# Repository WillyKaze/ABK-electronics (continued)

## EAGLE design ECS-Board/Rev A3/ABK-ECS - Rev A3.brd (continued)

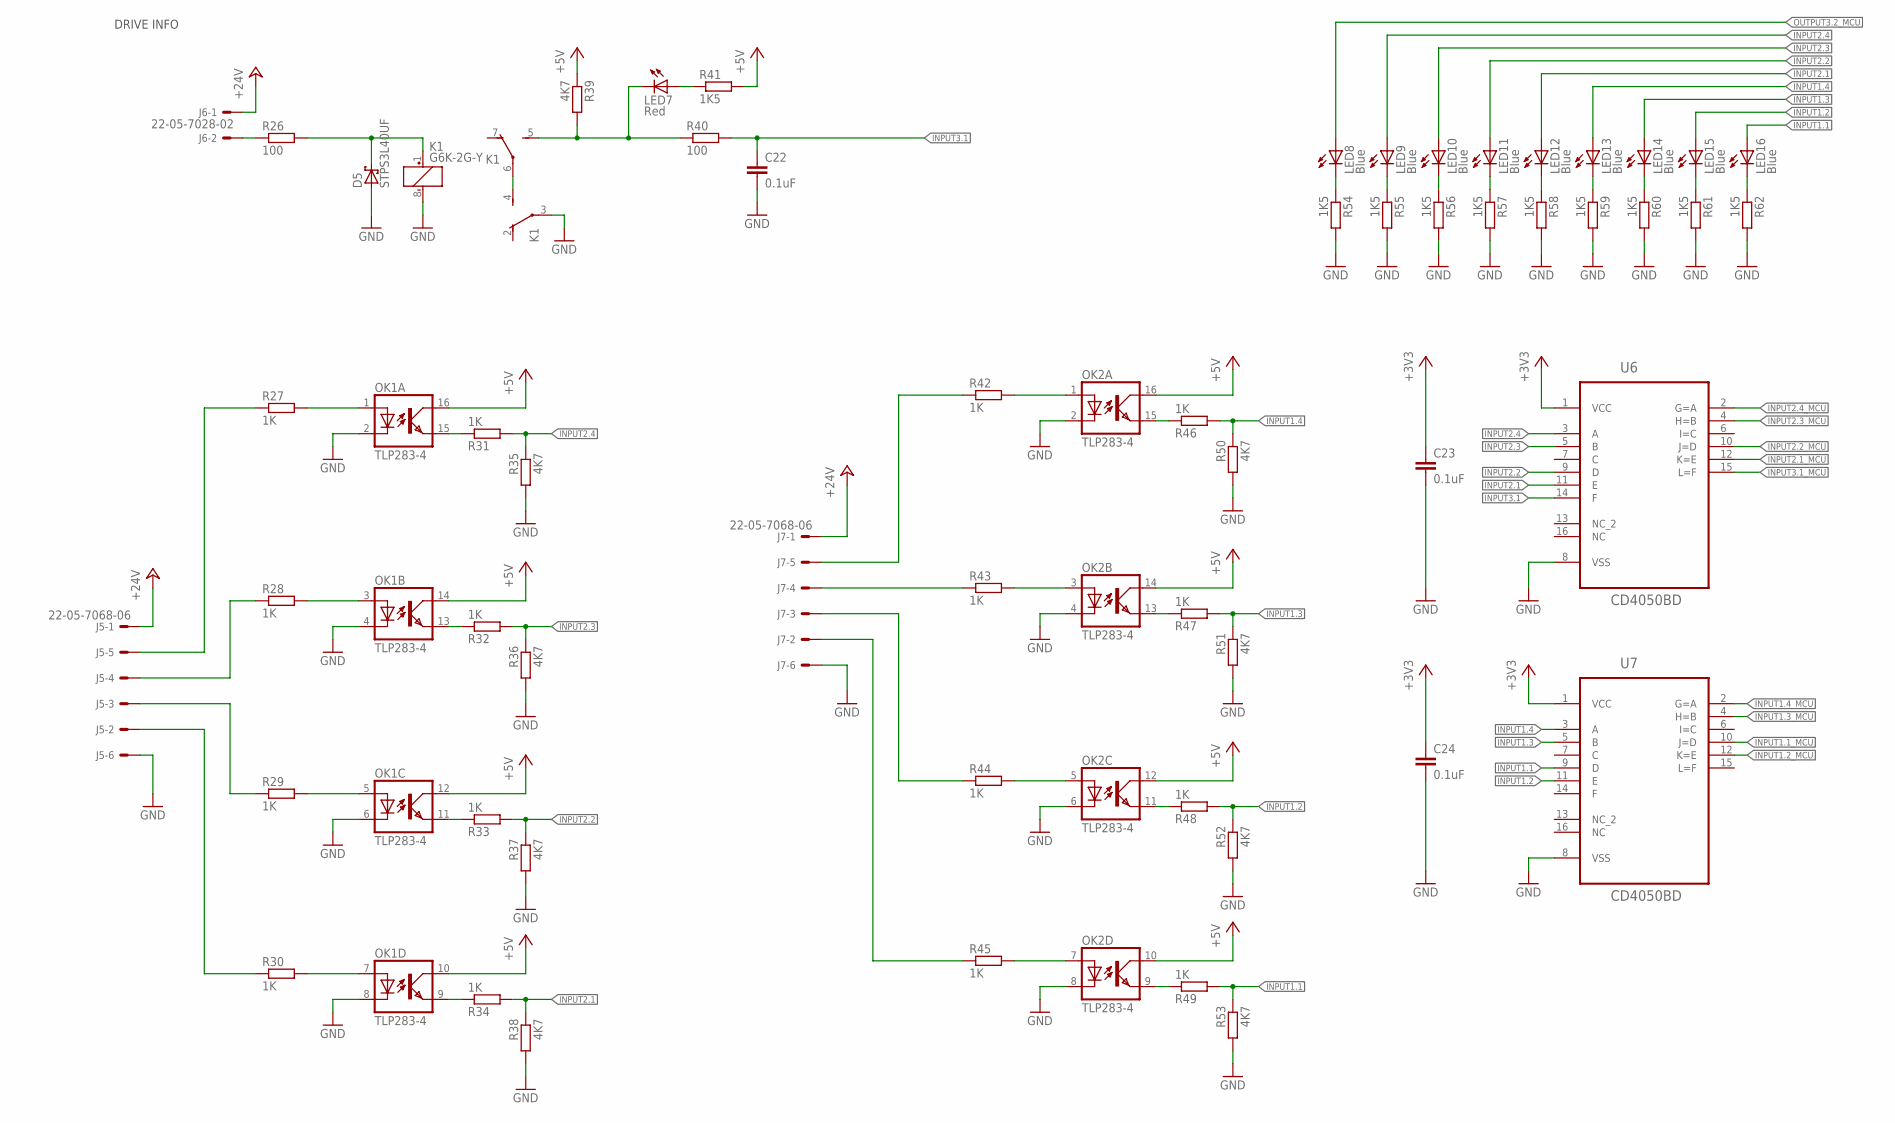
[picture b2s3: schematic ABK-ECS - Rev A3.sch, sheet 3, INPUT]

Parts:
C22, C23, C24: 0.1uF; C0603; MPN MC0603B104K160CT
D5: STPS3L40UF; SMB
J5, J7: 22-05-7068-06; 7395-06
J6: 22-05-7028-02; 7395-02; MPN 22-05-7028
K1: G6K-2G-Y; MPN G6K-2G-Y 24DC
LED7: Red; CHIPLED_0603; MPN OVS-0608
LED8, LED9, LED10, LED11, LED12, LED13, LED14, LED15, LED16: Blue; CHIPLED_0603; MPN OVS-0603
OK1, OK2: TLP283-4; MINI-FLAT-16; MPN TCMT4100
R26, R40: 100; R0603; MPN RC0603FR-13100RL
R27, R28, R29, R30, R31, R32, R33, R34, R42, R43, R44, R45, R46, R47, R48, R49: 1K; R0603; MPN RC0603FR-071KL
R35, R36, R37, R38, R39, R50, R51, R52, R53: 4K7; R0603; MPN RC0603FR-074K7L
R41, R54, R55, R56, R57, R58, R59, R60, R61, R62: 1K5; R0603; MPN RC0603FR-071K5L
U6, U7: CD4050BD; SOIC127P600X175-16N

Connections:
+3V3: C23.1, C24.1, U6.1 (VCC), U7.1 (VCC); also elsewhere on the board
+5V: OK1.10 (COL), OK1.12 (COL), OK1.14 (COL), OK1.16 (COL), OK2.10 (COL), OK2.12 (COL), OK2.14 (COL), OK2.16 (COL), R39.1, R41.2; also elsewhere on the board
+24V: J5.1, J6.1, J7.1; also elsewhere on the board
GND: C22.2, C23.2, C24.2, D5.A, J5.6, J7.6, K1.3, K1.8 (-), OK1.2 (C), OK1.4 (C), OK1.6 (C), OK1.8 (C), OK2.2 (C), OK2.4 (C), OK2.6 (C), OK2.8 (C), R35.2, R36.2, R37.2, R38.2, R50.2, R51.2, R52.2, R53.2, R54.2, R55.2, R56.2, R57.2, R58.2, R59.2, R60.2, R61.2, R62.2, U6.8 (VSS), U7.8 (VSS); also elsewhere on the board
INPUT1.1: LED16.A, R49.2, R53.1, U7.9 (D)
INPUT1.1_MCU: U7.10 (J=D); also elsewhere on the board
INPUT1.2: LED15.A, R48.2, R52.1, U7.11 (E)
INPUT1.2_MCU: U7.12 (K=E); also elsewhere on the board
INPUT1.3: LED14.A, R47.2, R51.1, U7.5 (B)
INPUT1.3_MCU: U7.4 (H=B); also elsewhere on the board
INPUT1.4: LED13.A, R46.2, R50.1, U7.3 (A)
INPUT1.4_MCU: U7.2 (G=A); also elsewhere on the board
INPUT2.1: LED12.A, R34.2, R38.1, U6.11 (E)
INPUT2.1_MCU: U6.12 (K=E); also elsewhere on the board
INPUT2.2: LED11.A, R33.2, R37.1, U6.9 (D)
INPUT2.2_MCU: U6.10 (J=D); also elsewhere on the board
INPUT2.3: LED10.A, R32.2, R36.1, U6.5 (B)
INPUT2.3_MCU: U6.4 (H=B); also elsewhere on the board
INPUT2.4: LED9.A, R31.2, R35.1, U6.3 (A)
INPUT2.4_MCU: U6.2 (G=A); also elsewhere on the board
INPUT3.1: C22.1, R40.2, U6.14 (F)
INPUT3.1_MCU: U6.15 (L=F); also elsewhere on the board
unnamed: D5.C, K1.1 (+), R26.2
unnamed: J6.2, R26.1
unnamed: OK1.1 (A), R27.2
unnamed: OK1.3 (A), R28.2
unnamed: OK1.5 (A), R29.2
unnamed: OK1.7 (A), R30.2
unnamed: J5.2, R30.1
unnamed: J5.3, R29.1
unnamed: J5.4, R28.1
unnamed: J5.5, R27.1
unnamed: LED8.C, R54.1
unnamed: LED9.C, R55.1
unnamed: LED10.C, R56.1
unnamed: LED11.C, R57.1
unnamed: K1.4 (S), K1.6
unnamed: OK1.9 (EMIT), R34.1
unnamed: OK1.11 (EMIT), R33.1
unnamed: OK1.13 (EMIT), R32.1
unnamed: OK1.15 (EMIT), R31.1
unnamed: LED12.C, R58.1
unnamed: K1.5 (S), LED7.C, R39.2, R40.1
unnamed: LED7.A, R41.1
unnamed: OK2.1 (A), R42.2
unnamed: J7.5, R42.1
unnamed: LED16.C, R62.1
unnamed: OK2.15 (EMIT), R46.1
unnamed: OK2.3 (A), R43.2
unnamed: J7.4, R43.1
unnamed: OK2.13 (EMIT), R47.1
unnamed: OK2.5 (A), R44.2
unnamed: J7.3, R44.1
unnamed: OK2.11 (EMIT), R48.1
unnamed: LED13.C, R59.1
unnamed: LED14.C, R60.1
unnamed: LED15.C, R61.1
unnamed: OK2.9 (EMIT), R49.1
unnamed: OK2.7 (A), R45.2
unnamed: J7.2, R45.1
OUTPUT3.2_MCU: LED8.A; also elsewhere on the board

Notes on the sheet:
DRIVE INFO

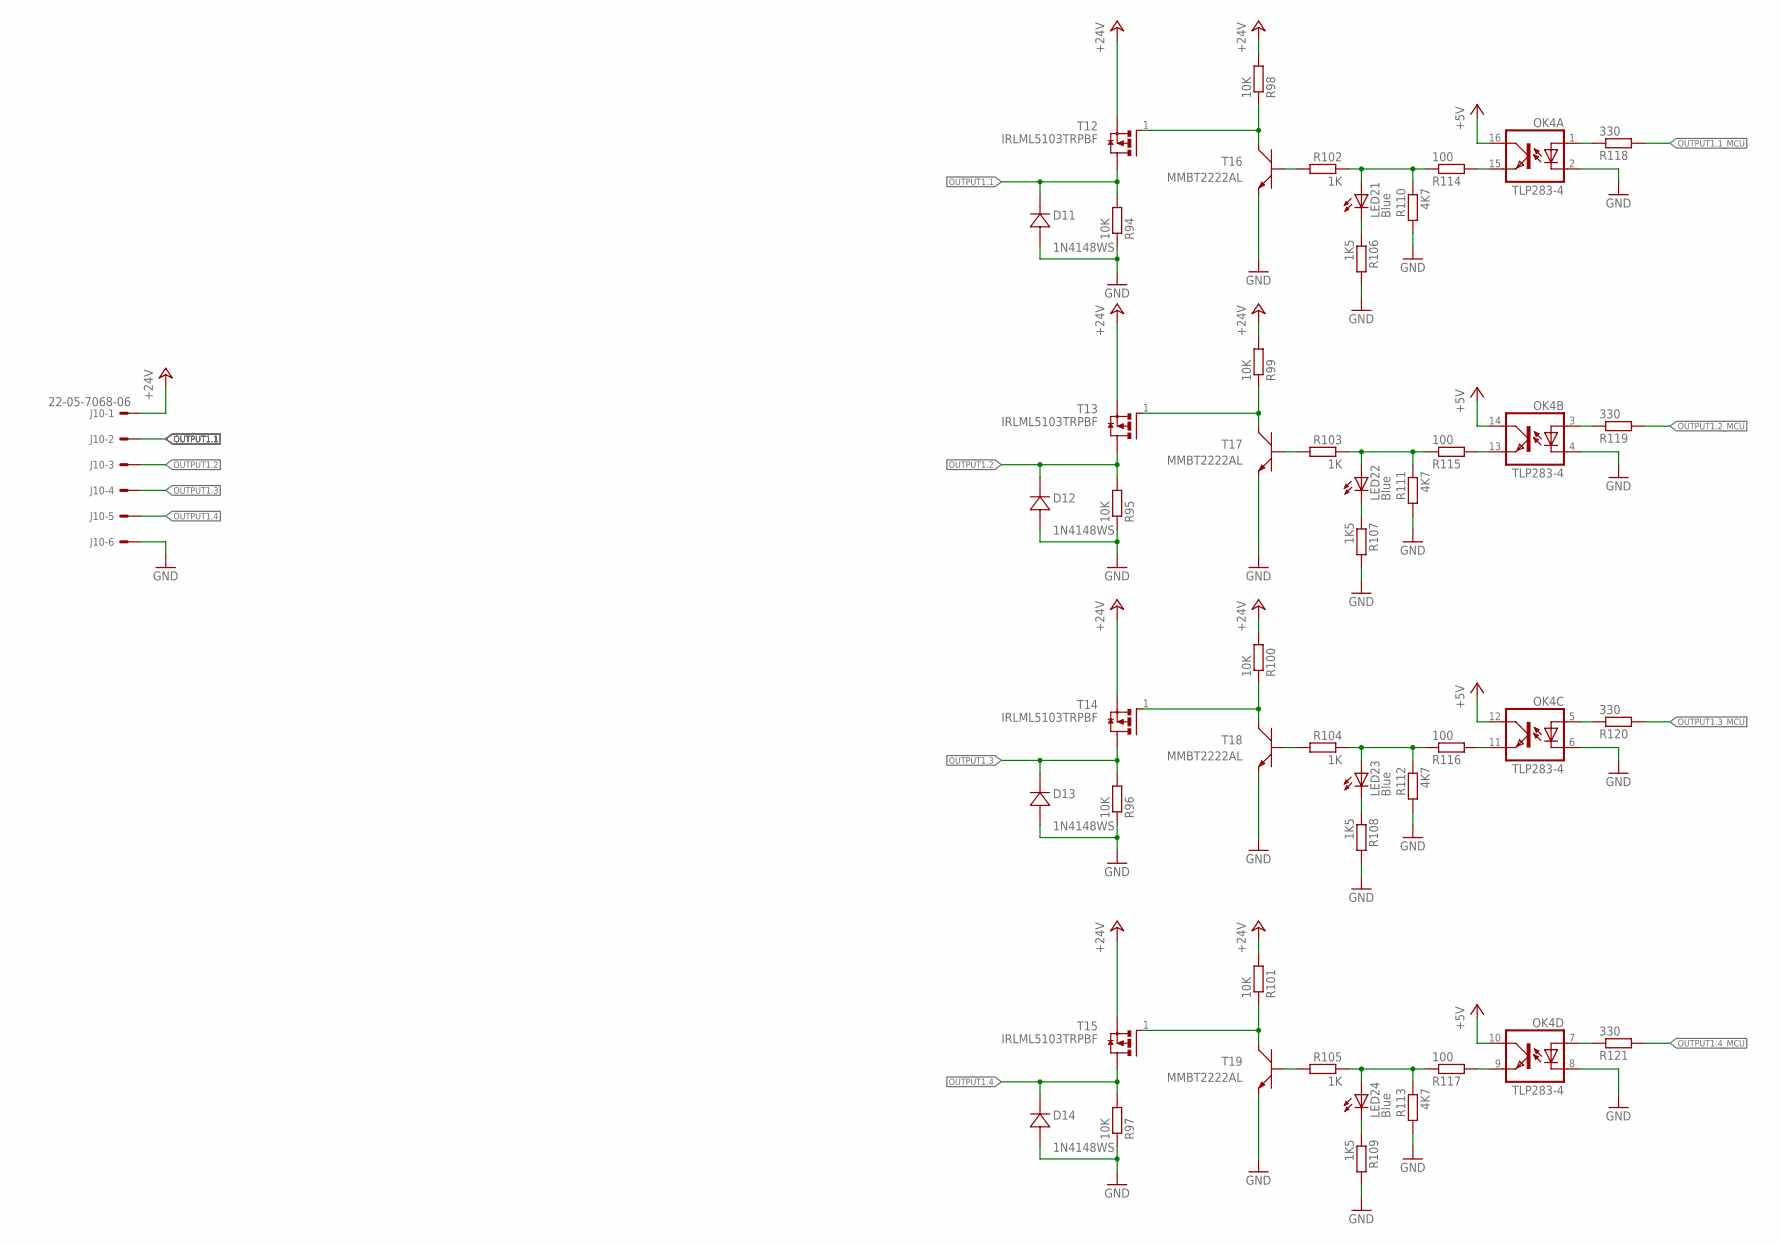
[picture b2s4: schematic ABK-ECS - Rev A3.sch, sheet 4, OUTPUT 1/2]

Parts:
D11, D12, D13, D14: 1N4148WS; SOD323-W; MPN 1N4148WS
J10: 22-05-7068-06; 7395-06
LED21, LED22, LED23, LED24: Blue; CHIPLED_0603; MPN OVS-0603
OK4: TLP283-4; MINI-FLAT-16; MPN TCMT4100
R94, R95, R96, R97, R98, R99, R100, R101: 10K; R0603; MPN RC0603FR-0710KL
R102, R103, R104, R105: 1K; R0603; MPN RC0603FR-071KL
R106, R107, R108, R109: 1K5; R0603; MPN RC0603FR-071K5L
R110, R111, R112, R113: 4K7; R0603; MPN RC0603FR-074K7L
R114, R115, R116, R117: 100; R0603; MPN RC0603FR-13100RL
R118, R119, R120, R121: 330; R0603; MPN RC0603FR-07330RL
T12, T13, T14, T15: IRLML5103TRPBF; SOT95P240X112-3N; MPN IRLML5103TRPBF
T16, T17, T18, T19: MMBT2222AL; SOT−23; MPN MMBT2222ALT1G

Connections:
+5V: OK4.10 (COL), OK4.12 (COL), OK4.14 (COL), OK4.16 (COL); also elsewhere on the board
+24V: J10.1, R98.2, R99.2, R100.2, R101.2, T12.2 (S), T13.2 (S), T14.2 (S), T15.2 (S); also elsewhere on the board
GND: D11.A (2), D12.A (2), D13.A (2), D14.A (2), J10.6, OK4.2 (C), OK4.4 (C), OK4.6 (C), OK4.8 (C), R94.1, R95.1, R96.1, R97.1, R106.2, R107.2, R108.2, R109.2, R110.2, R111.2, R112.2, R113.2, T16.2 (E), T17.2 (E), T18.2 (E), T19.2 (E); also elsewhere on the board
unnamed: LED21.A, R102.1, R110.1, R114.1
unnamed: OK4.15 (EMIT), R114.2
unnamed: LED22.A, R103.1, R111.1, R115.1
unnamed: OK4.13 (EMIT), R115.2
unnamed: LED23.A, R104.1, R112.1, R116.1
unnamed: LED24.A, R105.1, R113.1, R117.1
unnamed: OK4.11 (EMIT), R116.2
unnamed: OK4.9 (EMIT), R117.2
unnamed: OK4.1 (A), R118.1
unnamed: OK4.3 (A), R119.1
unnamed: OK4.7 (A), R121.1
unnamed: OK4.5 (A), R120.1
unnamed: LED21.C, R106.1
unnamed: LED22.C, R107.1
unnamed: LED23.C, R108.1
unnamed: LED24.C, R109.1
unnamed: R98.1, T12.1 (G), T16.3 (C)
unnamed: R99.1, T13.1 (G), T17.3 (C)
unnamed: R100.1, T14.1 (G), T18.3 (C)
unnamed: R101.1, T15.1 (G), T19.3 (C)
unnamed: R102.2, T16.1 (B)
unnamed: R103.2, T17.1 (B)
unnamed: R104.2, T18.1 (B)
unnamed: R105.2, T19.1 (B)
OUTPUT1.1: D11.C (1), J10.2, R94.2, T12.3 (D)
OUTPUT1.1_MCU: R118.2; also elsewhere on the board
OUTPUT1.2: D12.C (1), J10.3, R95.2, T13.3 (D)
OUTPUT1.2_MCU: R119.2; also elsewhere on the board
OUTPUT1.3: D13.C (1), J10.4, R96.2, T14.3 (D)
OUTPUT1.3_MCU: R120.2; also elsewhere on the board
OUTPUT1.4: D14.C (1), J10.5, R97.2, T15.3 (D)
OUTPUT1.4_MCU: R121.2; also elsewhere on the board

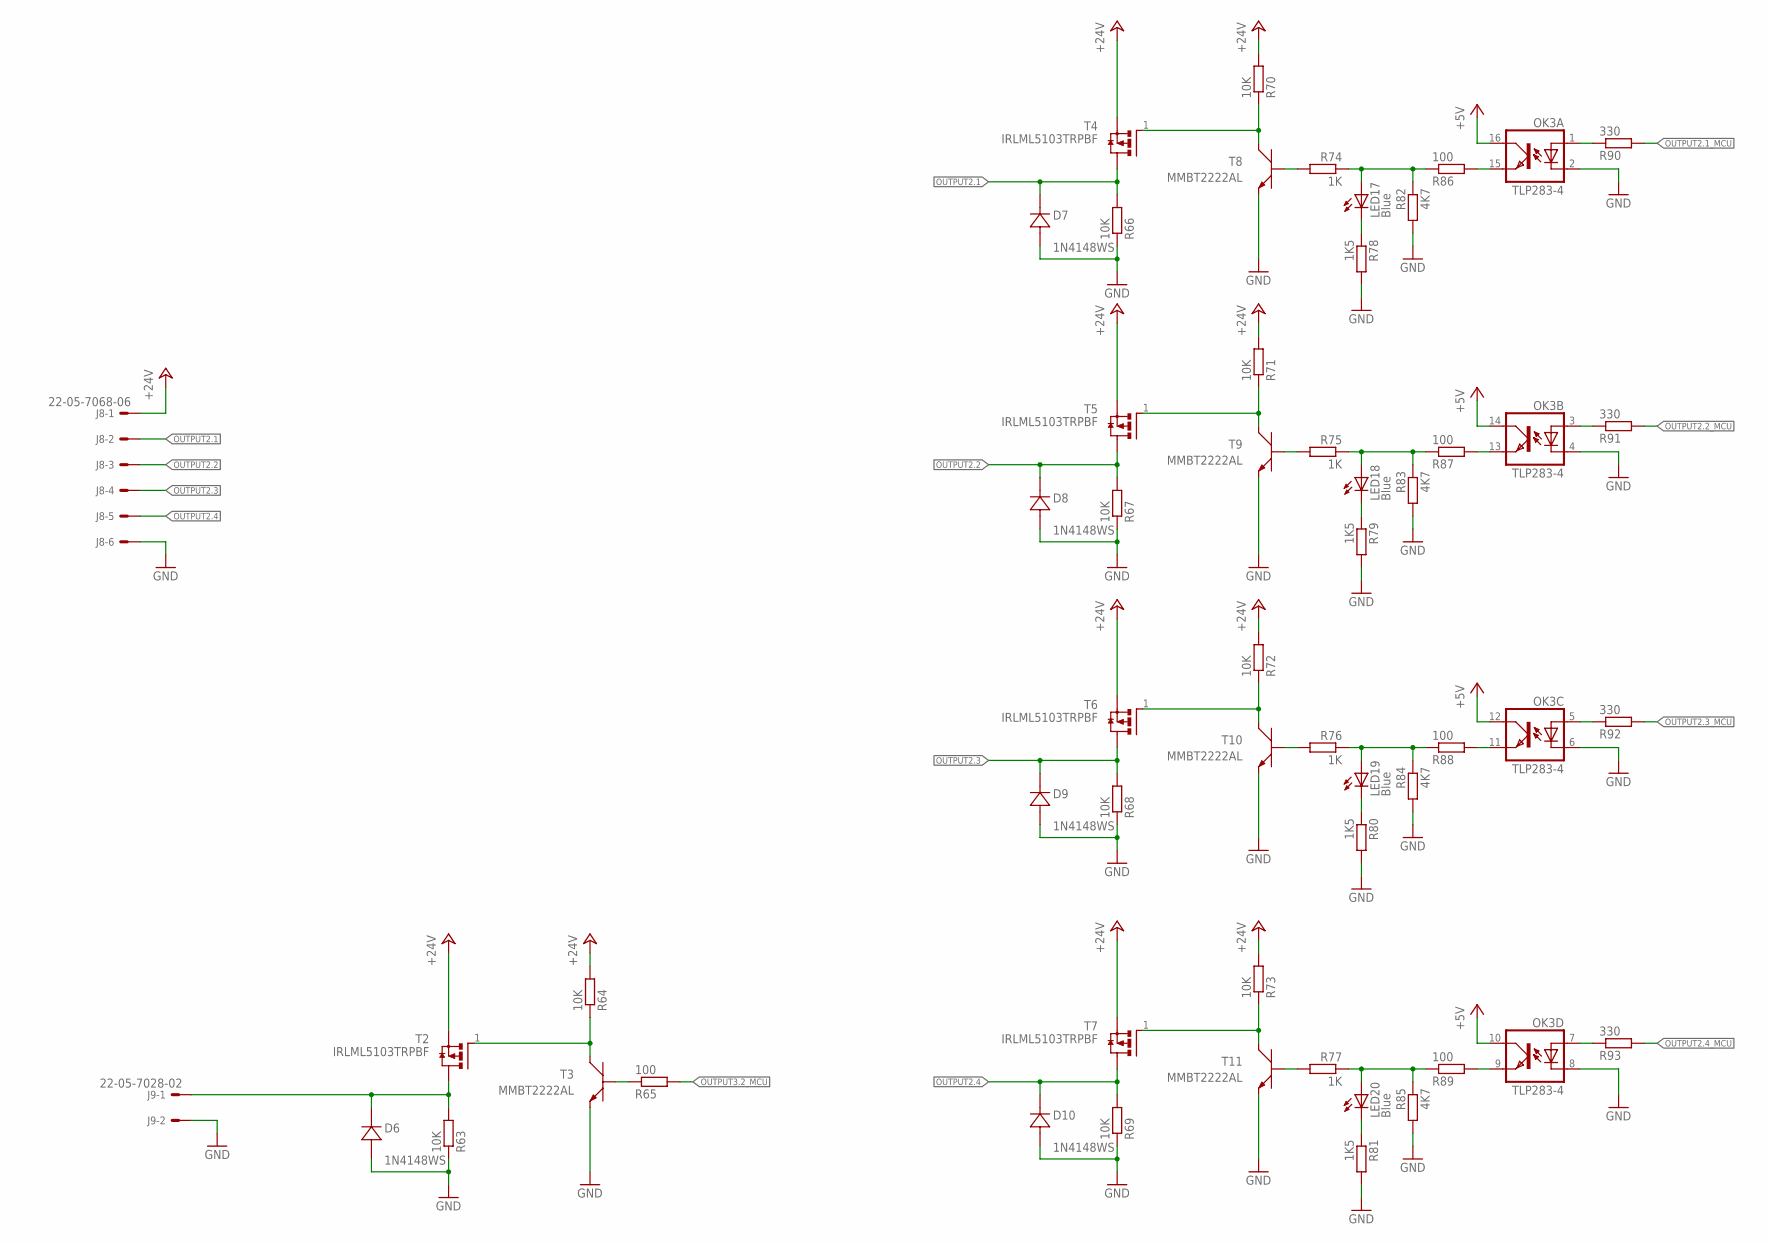
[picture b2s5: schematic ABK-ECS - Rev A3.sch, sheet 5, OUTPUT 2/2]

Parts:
D6, D7, D8, D9, D10: 1N4148WS; SOD323-W; MPN 1N4148WS
J8: 22-05-7068-06; 7395-06
J9: 22-05-7028-02; 7395-02; MPN 22-05-7028
LED17, LED18, LED19, LED20: Blue; CHIPLED_0603; MPN OVS-0603
OK3: TLP283-4; MINI-FLAT-16; MPN TCMT4100
R63, R64, R66, R67, R68, R69, R70, R71, R72, R73: 10K; R0603; MPN RC0603FR-0710KL
R65, R86, R87, R88, R89: 100; R0603; MPN RC0603FR-13100RL
R74, R75, R76, R77: 1K; R0603; MPN RC0603FR-071KL
R78, R79, R80, R81: 1K5; R0603; MPN RC0603FR-071K5L
R82, R83, R84, R85: 4K7; R0603; MPN RC0603FR-074K7L
R90, R91, R92, R93: 330; R0603; MPN RC0603FR-07330RL
T2, T4, T5, T6, T7: IRLML5103TRPBF; SOT95P240X112-3N; MPN IRLML5103TRPBF
T3, T8, T9, T10, T11: MMBT2222AL; SOT−23; MPN MMBT2222ALT1G

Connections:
+5V: OK3.10 (COL), OK3.12 (COL), OK3.14 (COL), OK3.16 (COL); also elsewhere on the board
+24V: J8.1, R64.2, R70.2, R71.2, R72.2, R73.2, T2.2 (S), T4.2 (S), T5.2 (S), T6.2 (S), T7.2 (S); also elsewhere on the board
GND: D6.A (2), D7.A (2), D8.A (2), D9.A (2), D10.A (2), J8.6, J9.2, OK3.2 (C), OK3.4 (C), OK3.6 (C), OK3.8 (C), R63.1, R66.1, R67.1, R68.1, R69.1, R78.2, R79.2, R80.2, R81.2, R82.2, R83.2, R84.2, R85.2, T3.2 (E), T8.2 (E), T9.2 (E), T10.2 (E), T11.2 (E); also elsewhere on the board
MOTOR_VFQ: D6.C (1), J9.1, R63.2, T2.3 (D)
unnamed: R74.2, T8.1 (B)
unnamed: R70.1, T4.1 (G), T8.3 (C)
unnamed: R75.2, T9.1 (B)
unnamed: R71.1, T5.1 (G), T9.3 (C)
unnamed: R76.2, T10.1 (B)
unnamed: R72.1, T6.1 (G), T10.3 (C)
unnamed: R77.2, T11.1 (B)
unnamed: R73.1, T7.1 (G), T11.3 (C)
unnamed: R65.1, T3.1 (B)
unnamed: R64.1, T2.1 (G), T3.3 (C)
unnamed: LED17.A, R74.1, R82.1, R86.1
unnamed: OK3.15 (EMIT), R86.2
unnamed: LED18.A, R75.1, R83.1, R87.1
unnamed: OK3.13 (EMIT), R87.2
unnamed: LED19.A, R76.1, R84.1, R88.1
unnamed: LED20.A, R77.1, R85.1, R89.1
unnamed: OK3.11 (EMIT), R88.2
unnamed: OK3.9 (EMIT), R89.2
unnamed: OK3.1 (A), R90.1
unnamed: OK3.3 (A), R91.1
unnamed: OK3.7 (A), R93.1
unnamed: OK3.5 (A), R92.1
unnamed: LED17.C, R78.1
unnamed: LED18.C, R79.1
unnamed: LED19.C, R80.1
unnamed: LED20.C, R81.1
OUTPUT2.1: D7.C (1), J8.2, R66.2, T4.3 (D)
OUTPUT2.1_MCU: R90.2; also elsewhere on the board
OUTPUT2.2: D8.C (1), J8.3, R67.2, T5.3 (D)
OUTPUT2.2_MCU: R91.2; also elsewhere on the board
OUTPUT2.3: D9.C (1), J8.4, R68.2, T6.3 (D)
OUTPUT2.3_MCU: R92.2; also elsewhere on the board
OUTPUT2.4: D10.C (1), J8.5, R69.2, T7.3 (D)
OUTPUT2.4_MCU: R93.2; also elsewhere on the board
OUTPUT3.2_MCU: R65.2; also elsewhere on the board

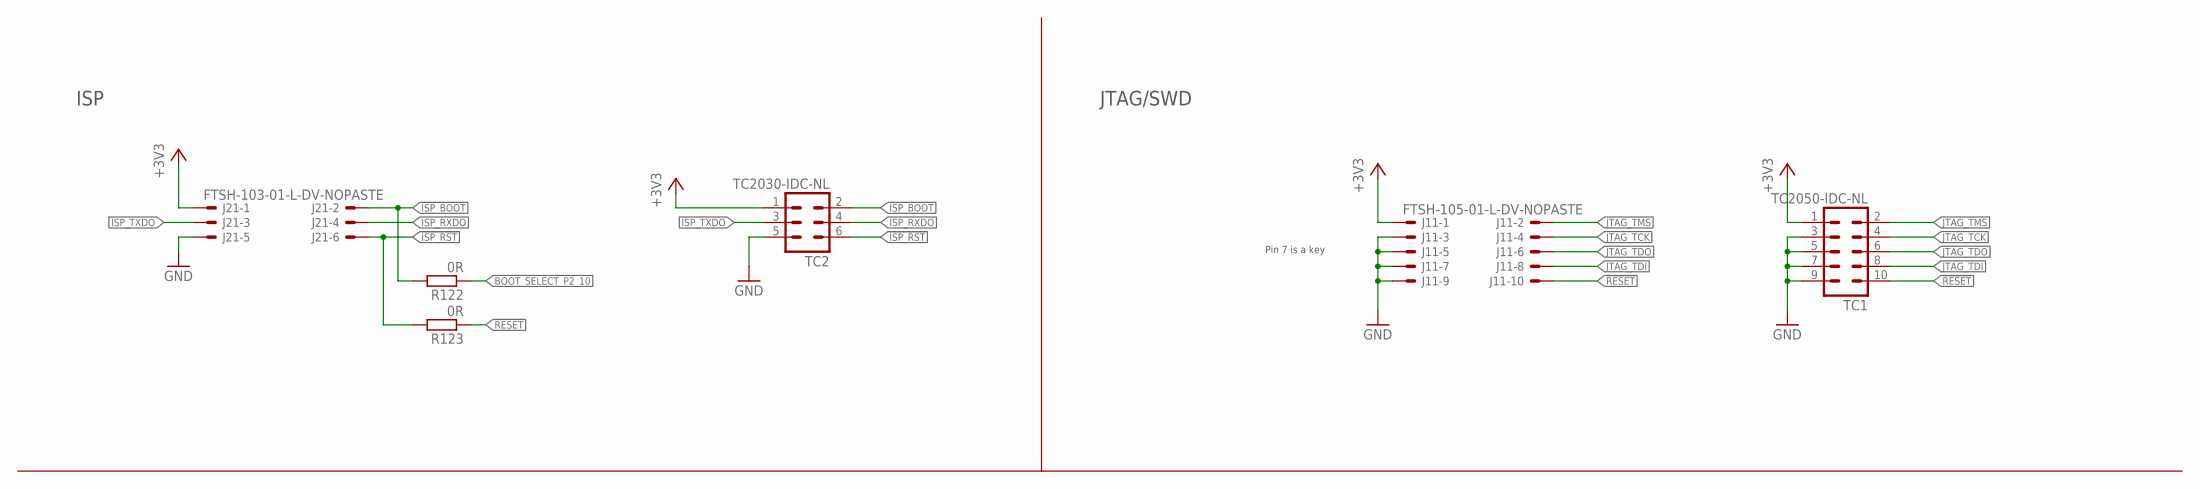
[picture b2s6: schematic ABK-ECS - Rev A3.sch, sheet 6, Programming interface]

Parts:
J11: FTSH-105-01-L-DV-NOPASTE
J21: FTSH-103-01-L-DV-NOPASTE
R122, R123: 0R; R0603; MPN MCMR06X000 PTL
TC1: TC2050-IDC-NL
TC2: TC2030-IDC-NL

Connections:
!ISP_BOOT: J21.2, R122.2, TC2.2
!ISP_RST: J21.6, R123.2, TC2.6
!RESET: J11.10, R123.1, TC1.10; also elsewhere on the board
+3V3: J11.1, J21.1, TC1.1, TC2.1; also elsewhere on the board
BOOT_SELECT_P2_10: R122.1; also elsewhere on the board
GND: J11.3, J11.5, J11.7, J11.9, J21.5, TC1.3, TC1.5, TC1.7, TC1.9, TC2.5; also elsewhere on the board
ISP_RXDO: J21.4, TC2.4; also elsewhere on the board
ISP_TXDO: J21.3, TC2.3; also elsewhere on the board
JTAG_TCK: J11.4, TC1.4; also elsewhere on the board
JTAG_TDI: J11.8, TC1.8; also elsewhere on the board
JTAG_TDO: J11.6, TC1.6; also elsewhere on the board
JTAG_TMS: J11.2, TC1.2; also elsewhere on the board

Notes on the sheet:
JTAG/SWD
Pin 7 is a key
ISP

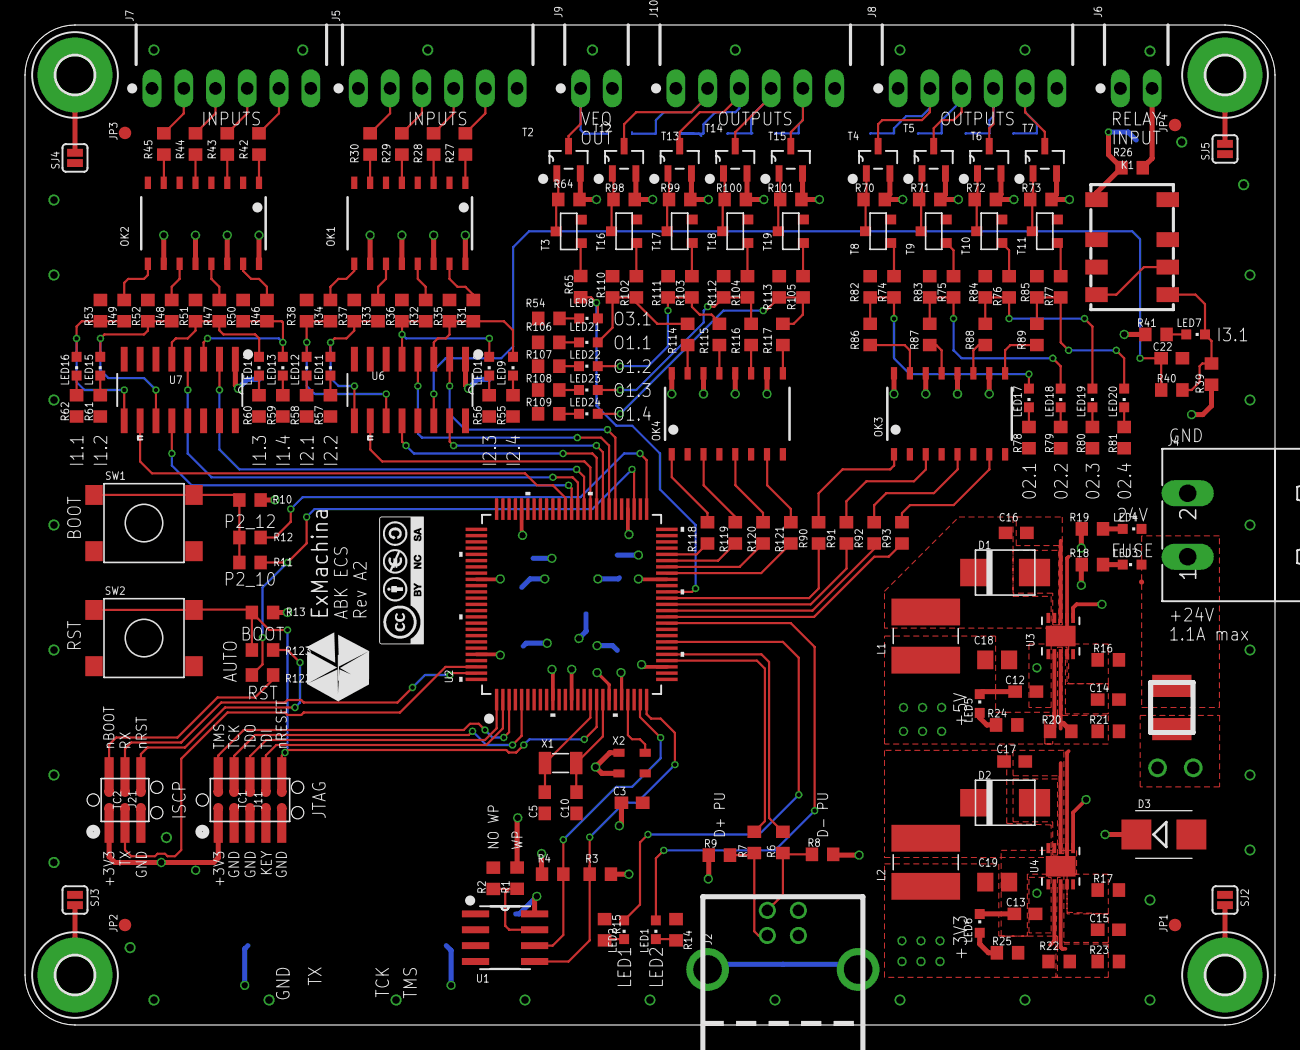
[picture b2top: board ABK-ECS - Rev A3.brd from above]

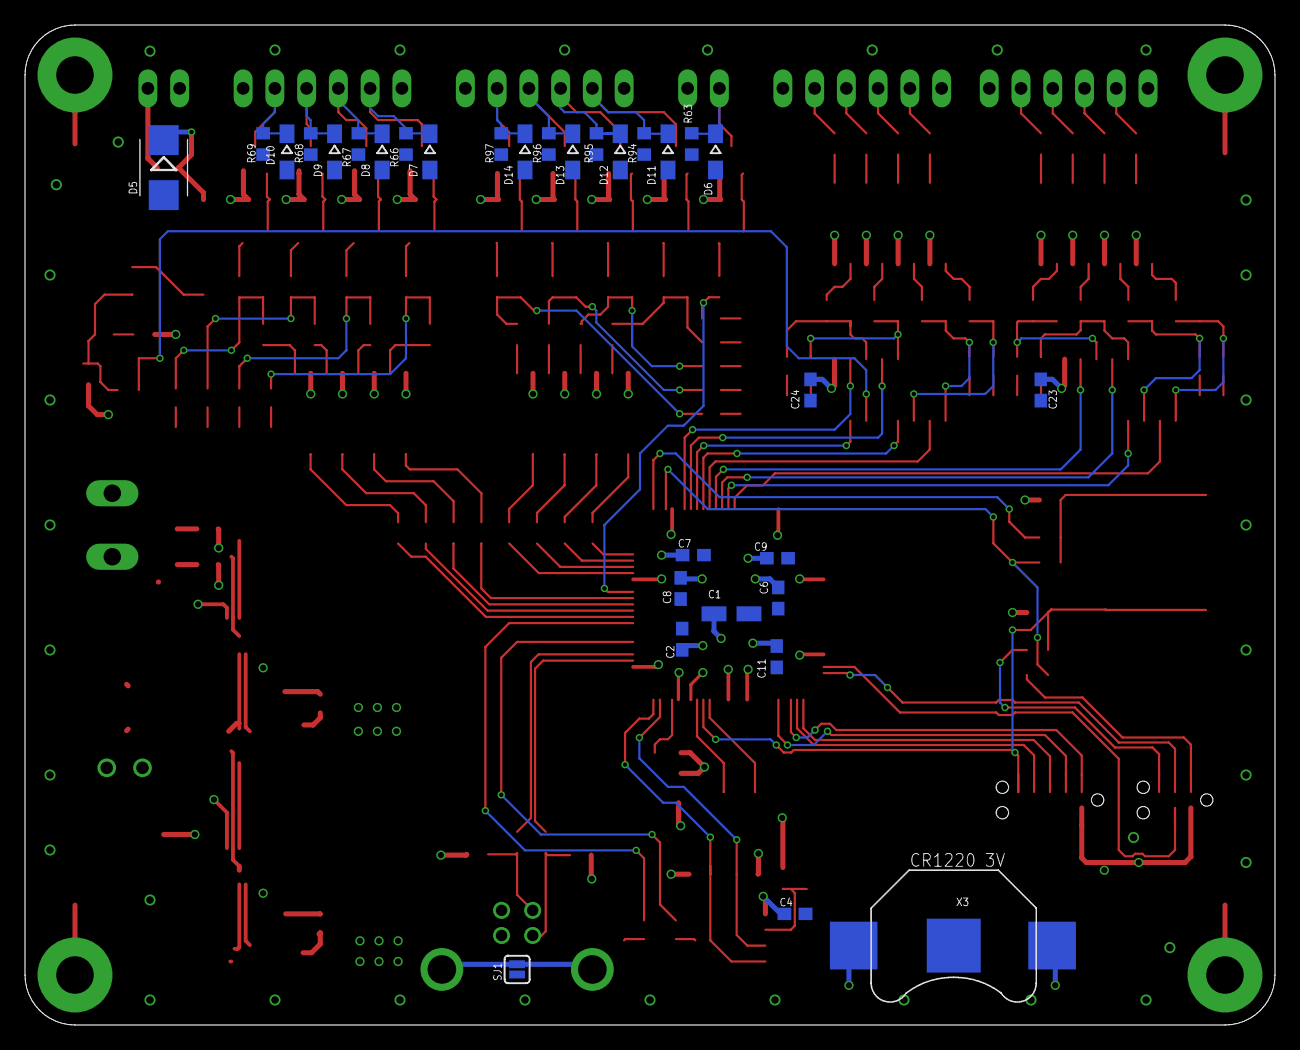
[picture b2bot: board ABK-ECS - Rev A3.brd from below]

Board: 4 copper layers, 100.0 x 80.0 mm, 245 parts (31 on the bottom side), 178 nets.

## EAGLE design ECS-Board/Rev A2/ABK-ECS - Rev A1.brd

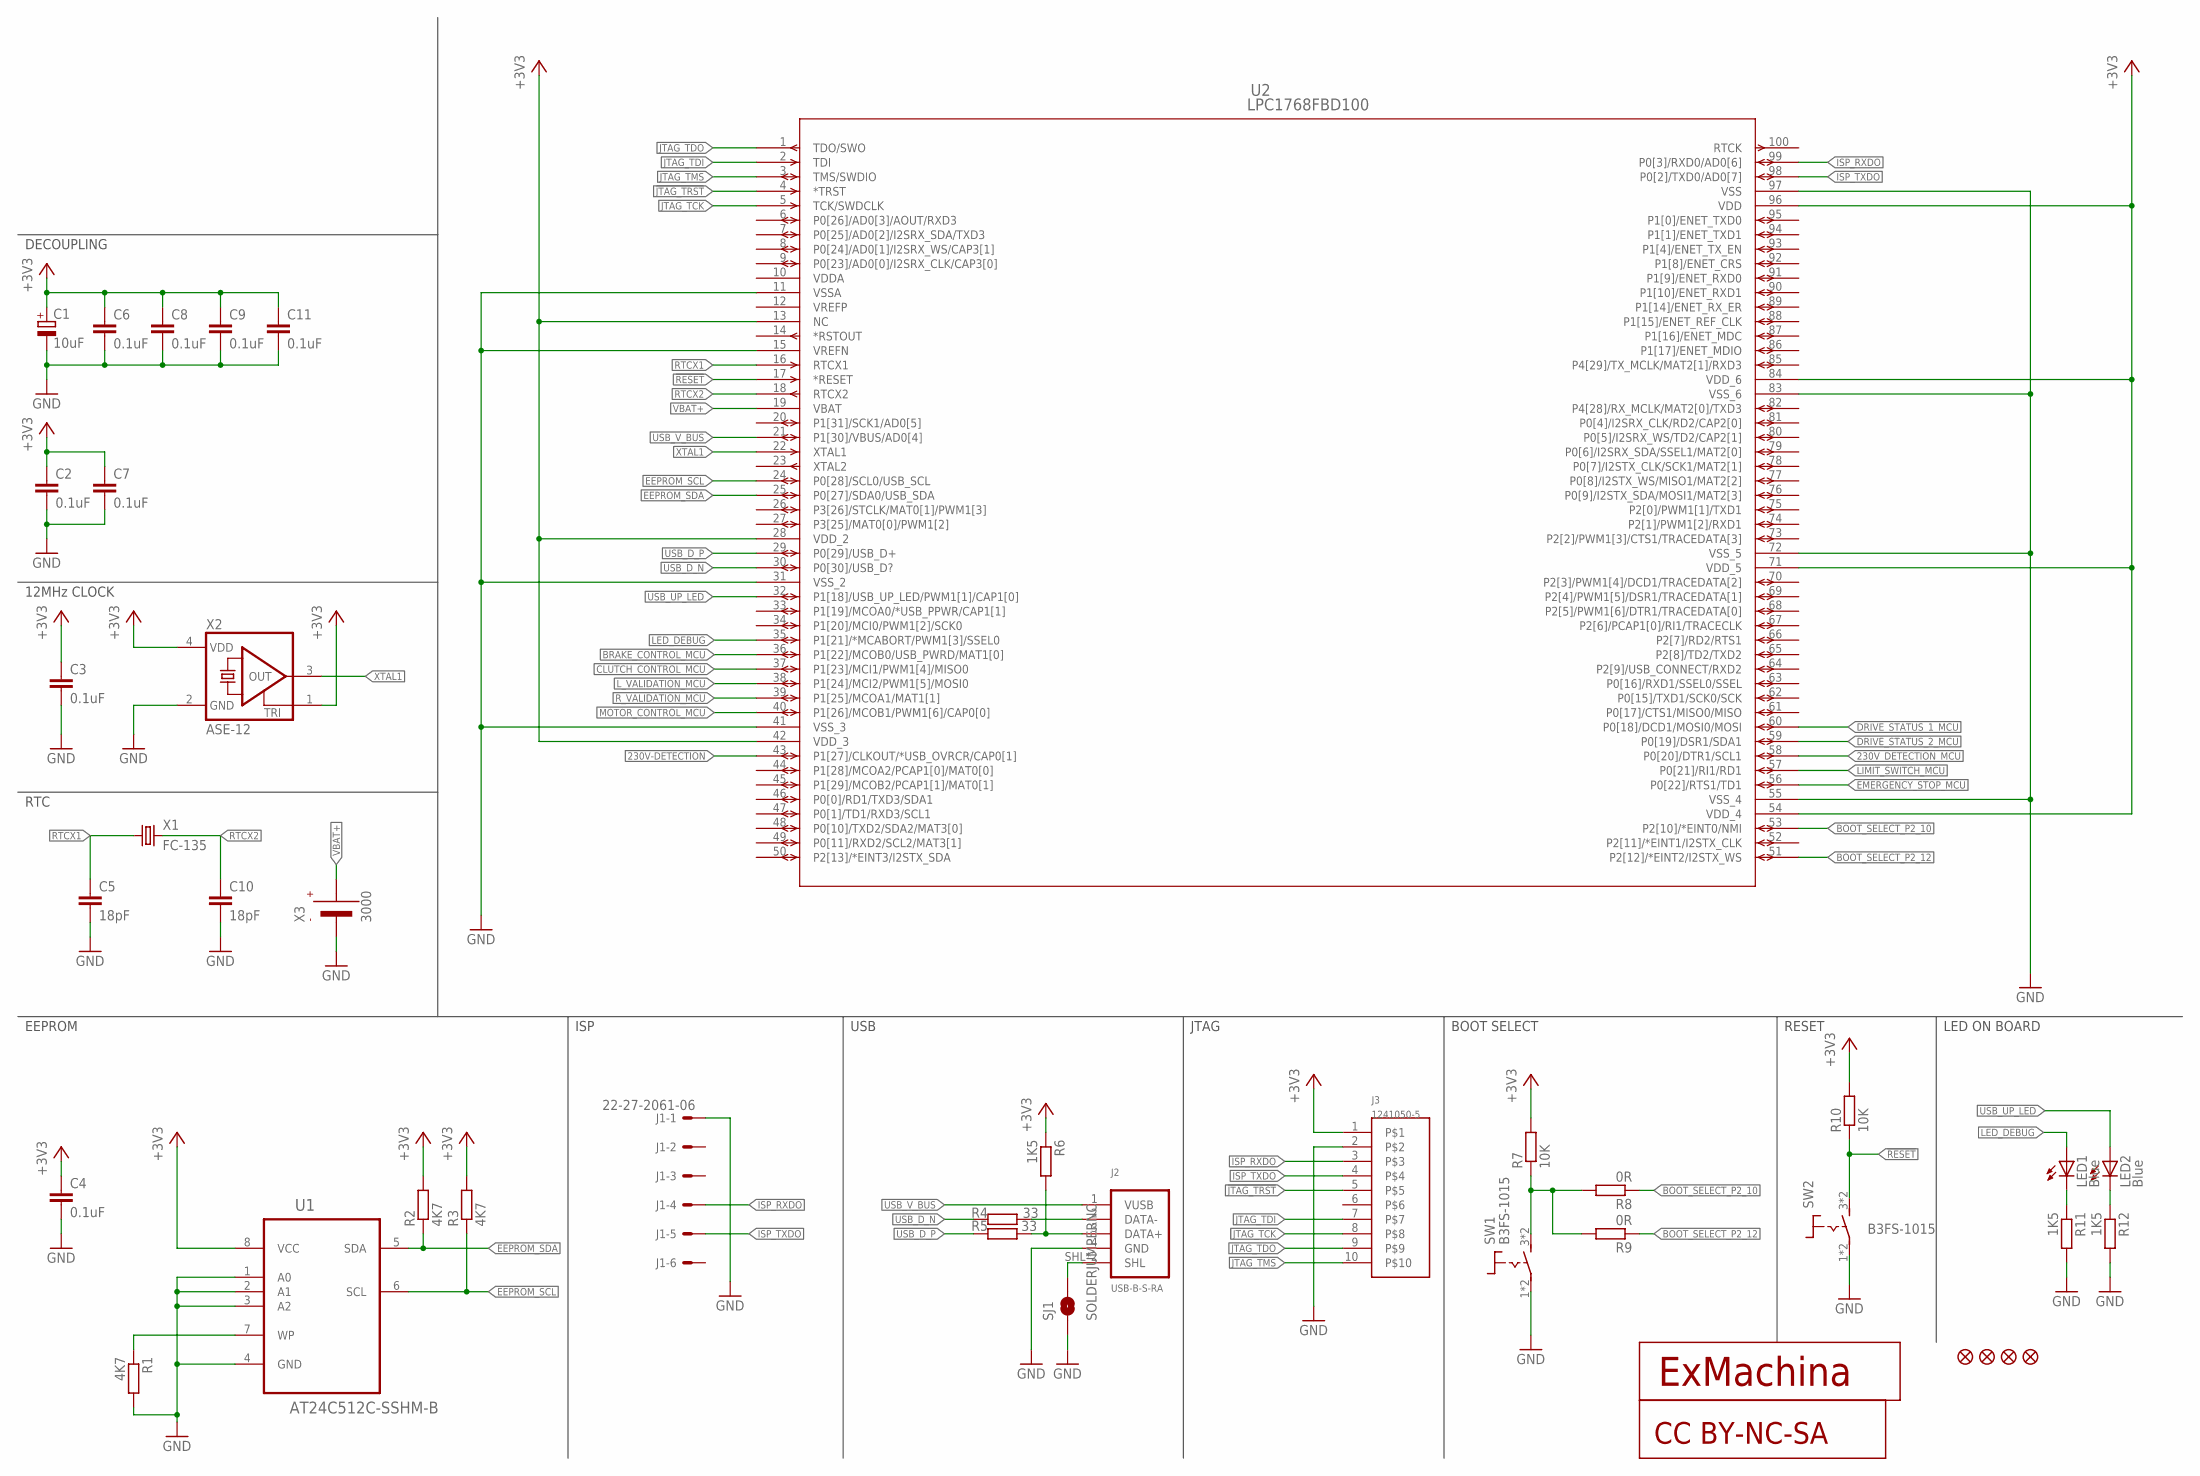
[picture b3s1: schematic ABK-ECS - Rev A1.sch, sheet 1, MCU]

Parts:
C1: 10uF; CT3216; MPN F931A106MAA
C2, C3, C4, C6, C7, C8, C9, C11: 0.1uF; C0603; MPN MC0603B104K160CT
C5, C10: 18pF; C0603; MPN MC0603N180K500CT
CC1: CC-BY-NC-SA
J1: 22-27-2061-06; 6410-06; MPN 22-27-2061
J2: USB-B-S-RA; MPN USB-B-S-RA
J3: 1241050-5; 2.54/2X5; MPN 1241050-5
JP1, JP2, JP3, JP4: FIDUCIAL1X2; FIDUCIAL-1X2
LED1, LED2: Blue; CHIPLED_0603; MPN OVS-0603
R1, R2, R3: 4K7; R0603; MPN MCMR06X4701FTL
R4, R5: 33; R0603; MPN MCMR06X33R0FTL
R6, R11, R12: 1K5; R0603; MPN MCMR06X1501FTL
R7, R10: 10K; R0603; MPN MCMR06X1002FTL
R8, R9: 0R; R0603; MPN MCMR06X000 PTL
SJ1: SOLDERJUMPERNC; SJ_2S
SW1, SW2: B3FS-1015; B3FS; MPN B3FS-1010
T1: EXMACHINA-LOGO-NAME; EXM-LOGO-BASELINE
U1: AT24C512C-SSHM-B; SOIC127P600X175-8N
U2: LPC1768FBD100; SOT407-1; MPN LPC1768FBD100
X1: FC-135; MPN Q13FC13500004
X2: ASE-12; ASE; MPN ASE-12.000MHZ-LC-T
X3: 3000; MPN 3000

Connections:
230V-DETECTION: U2.43 (P1[27]/CLKOUT/*USB_OVRCR/CAP0[1]); also elsewhere on the board
230V_DETECTION_MCU: U2.58 (P0[20]/DTR1/SCL1); also elsewhere on the board
!JTAG_TRST: J3.5, U2.4 (*TRST)
!RESET: R10.1, SW2.3 (1), SW2.4 (1), U2.17 (*RESET)
+3V3: C1.+, C2.1, C3.1, C4.1, C6.1, C7.1, C8.1, C9.1, C11.1, J3.1, R2.2, R3.2, R6.1, R7.2, R10.2, U1.8 (VCC), U2.13 (NC), U2.28 (VDD_2), U2.42 (VDD_3), U2.54 (VDD_4), U2.71 (VDD_5), U2.84 (VDD_6), U2.96 (VDD), X2.1 (TRI), X2.4 (VDD); also elsewhere on the board
BOOT_SELECT_P2_10: R8.1, U2.53 (P2[10]/*EINT0/NMI)
BOOT_SELECT_P2_12: R9.1, U2.51 (P2[12]/*EINT2/I2STX_WS)
BRAKE_CONTROL_MCU: U2.36 (P1[22]/MCOB0/USB_PWRD/MAT1[0]); also elsewhere on the board
CLUTCH_CONTROL_MCU: U2.37 (P1[23]/MCI1/PWM1[4]/MISO0); also elsewhere on the board
DRIVE_STATUS_1_MCU: U2.60 (P0[18]/DCD1/MOSI0/MOSI); also elsewhere on the board
DRIVE_STATUS_2_MCU: U2.59 (P0[19]/DSR1/SDA1); also elsewhere on the board
EEPROM_SCL: R3.1, U1.6 (SCL), U2.24 (P0[28]/SCL0/USB_SCL)
EEPROM_SDA: R2.1, U1.5 (SDA), U2.25 (P0[27]/SDA0/USB_SDA)
EMERGENCY_STOP_MCU: U2.56 (P0[22]/RTS1/TD1); also elsewhere on the board
GND: C1.-, C2.2, C3.2, C4.2, C5.2, C6.2, C7.2, C8.2, C9.2, C10.2, C11.2, J1.1, J2.4 (GND), J3.2, R1.2, R11.2, R12.2, SJ1.1, SW1.1 (2), SW1.2, SW2.1 (2), SW2.2, U1.1 (A0), U1.2 (A1), U1.3 (A2), U1.4 (GND), U2.11 (VSSA), U2.15 (VREFN), U2.31 (VSS_2), U2.41 (VSS_3), U2.55 (VSS_4), U2.72 (VSS_5), U2.83 (VSS_6), U2.97 (VSS), X2.2 (GND), X3.- (VBAT-); also elsewhere on the board
ISP_RXDO: J1.4, J3.3, U2.99 (P0[3]/RXD0/AD0[6])
ISP_TXDO: J1.5, J3.4, U2.98 (P0[2]/TXD0/AD0[7])
JTAG_TCK: J3.8, U2.5 (TCK/SWDCLK)
JTAG_TDI: J3.7, U2.2 (TDI)
JTAG_TDO: J3.9, U2.1 (TDO/SWO)
JTAG_TMS: J3.10, U2.3 (TMS/SWDIO)
LED_DEBUG: LED1.A, U2.35 (P1[21]/*MCABORT/PWM1[3]/SSEL0)
LIMIT_SWITCH_MCU: U2.57 (P0[21]/RI1/RD1); also elsewhere on the board
L_VALIDATION_MCU: U2.38 (P1[24]/MCI2/PWM1[5]/MOSI0); also elsewhere on the board
MOTOR_CONTROL_MCU: U2.40 (P1[26]/MCOB1/PWM1[6]/CAP0[0]); also elsewhere on the board
unnamed: J2.3 (DATA+), R5.1, R6.2
unnamed: J2.2 (DATA-), R4.1
unnamed: LED2.C, R12.1
unnamed: R7.1, R8.2, R9.2, SW1.3 (1), SW1.4 (1)
unnamed: R1.1, U1.7 (WP)
unnamed: LED1.C, R11.1
unnamed: J2.SHL, J2.SHL1 (SHL), SJ1.2
RTCX1: C5.1, U2.16 (RTCX1), X1.1
RTCX2: C10.1, U2.18 (RTCX2), X1.2
R_VALIDATION_MCU: U2.39 (P1[25]/MCOA1/MAT1[1]); also elsewhere on the board
USB_D_N: R4.2, U2.30 (P0[30]/USB_D?)
USB_D_P: R5.2, U2.29 (P0[29]/USB_D+)
USB_UP_LED: LED2.A, U2.32 (P1[18]/USB_UP_LED/PWM1[1]/CAP1[0])
USB_V_BUS: J2.1 (VUSB), U2.21 (P1[30]/VBUS/AD0[4])
VBAT+: U2.19 (VBAT), X3.+1 (VBAT+), X3.+2 (VBAT+)
VDDA: U2.10 (VDDA)
VREFP: U2.12 (VREFP)
XTAL1: U2.22 (XTAL1), X2.3 (OUT)

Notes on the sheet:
USB
JTAG
ISP
BOOT SELECT
LED ON BOARD
RESET
EEPROM
RTC
12MHz CLOCK
DECOUPLING
